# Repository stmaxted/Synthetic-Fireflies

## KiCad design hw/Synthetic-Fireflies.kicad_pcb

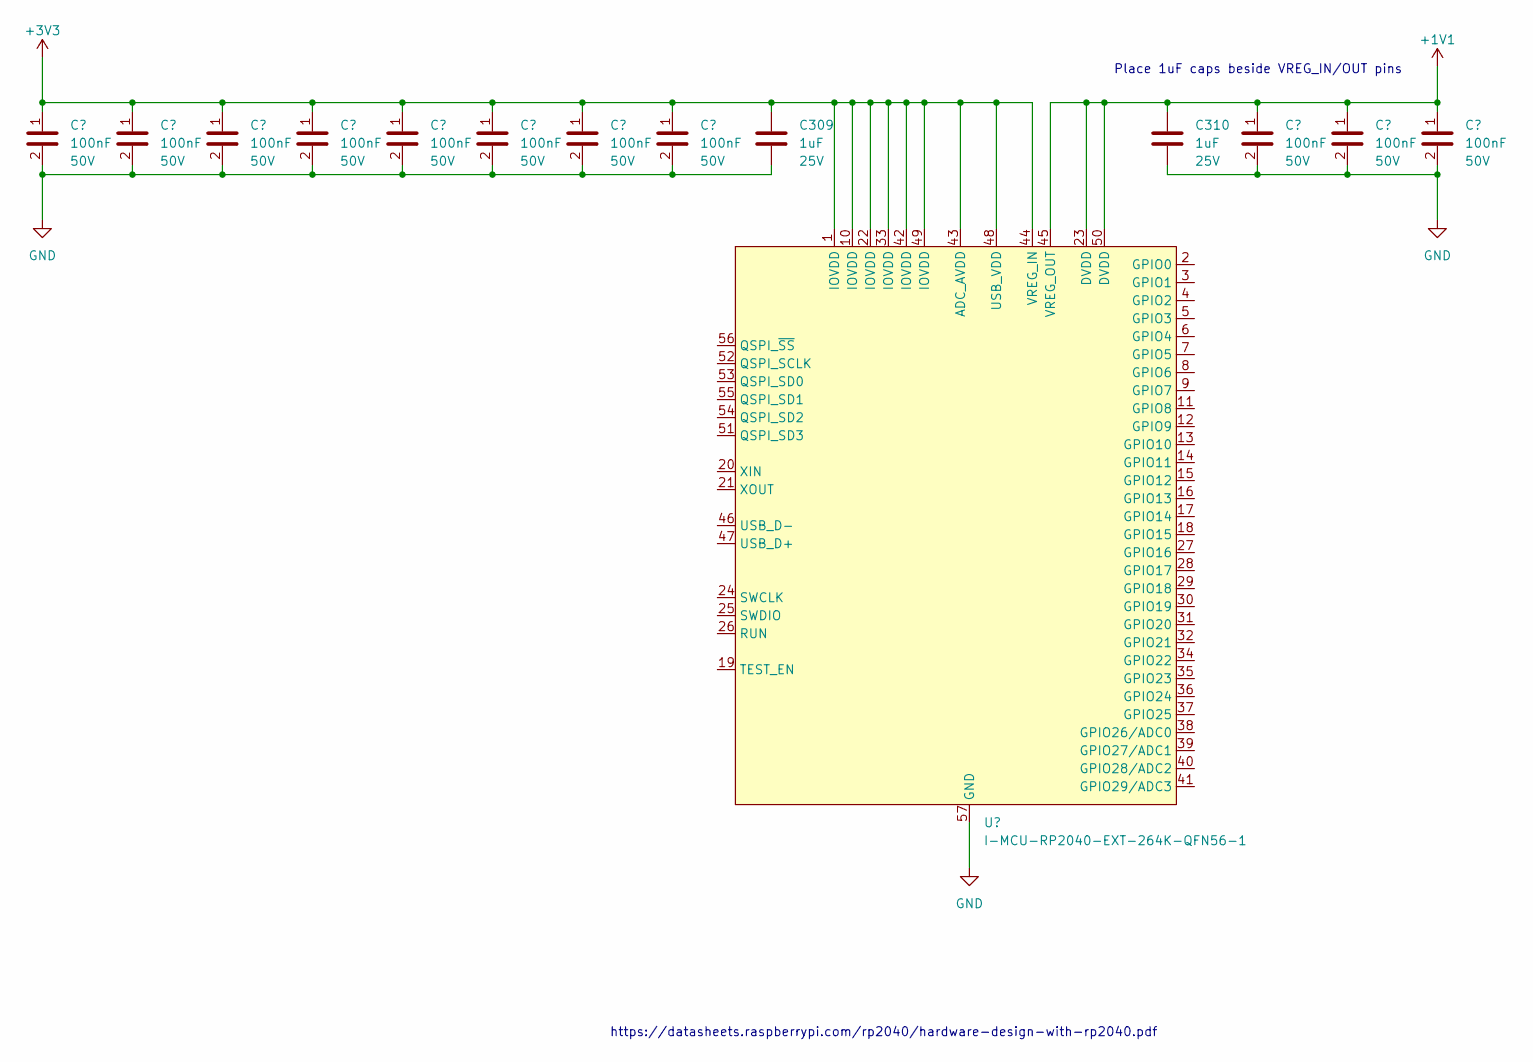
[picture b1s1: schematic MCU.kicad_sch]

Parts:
C301, C302, C303, C304, C305, C306, C307, C308, C311, C312, C313: C-0603-100NF-50V-1; C_0603_1608Metric; Voltage Rating 50V; Manufacturer Part Number CL10B104KB8NNNC
C309, C310: C-0603-1UF-25V-1; C_0603_1608Metric; Voltage Rating 25V; Manufacturer Part Number CL10A105KA8NNNC
U301: I-MCU-RP2040-EXT-264K-QFN56-1; QFN-56_1EP_7x7mm_P0.5mm; Manufacturer Part Number SC0914(13)

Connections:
+1V1: C310.1, C311.1, C312.1, C313.1, U301.23 (DVDD), U301.45 (VREG_OUT), U301.50 (DVDD)
+3V3: C301.1, C302.1, C303.1, C304.1, C305.1, C306.1, C307.1, C308.1, C309.1, U301.1 (IOVDD), U301.10 (IOVDD), U301.22 (IOVDD), U301.33 (IOVDD), U301.42 (IOVDD), U301.43 (ADC_AVDD), U301.44 (VREG_IN), U301.48 (USB_VDD), U301.49 (IOVDD)
GND: C301.2, C302.2, C303.2, C304.2, C305.2, C306.2, C307.2, C308.2, C309.2, C310.2, C311.2, C312.2, C313.2, U301.57 (GND)

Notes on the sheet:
https://datasheets.raspberrypi.com/rp2040/hardware-design-with-rp2040.pdf
Place 1uF caps beside VREG_IN/OUT pins

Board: 2 copper layers, 14 parts (0 on the bottom side), 3 nets, no tracks yet.

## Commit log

2023-01-28 MVP firmware
2023-02-11 Setup KiCAD project
2023-02-22 Complete MCU Power section of HW design guide
